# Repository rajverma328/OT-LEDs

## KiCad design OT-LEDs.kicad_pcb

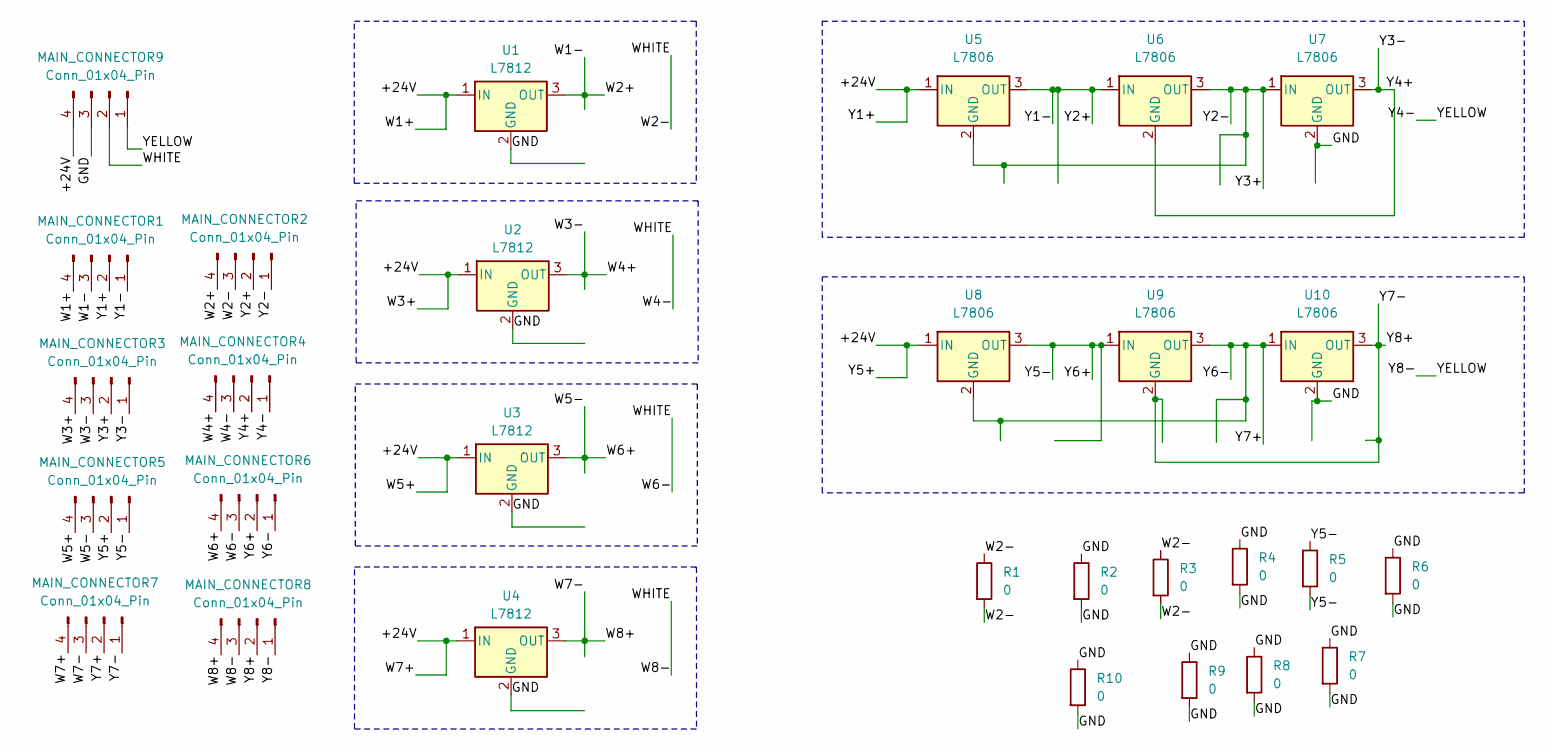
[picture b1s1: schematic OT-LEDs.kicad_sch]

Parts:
MAIN_CONNECTOR1, MAIN_CONNECTOR2, MAIN_CONNECTOR3, MAIN_CONNECTOR4, MAIN_CONNECTOR5, MAIN_CONNECTOR6, MAIN_CONNECTOR7, MAIN_CONNECTOR8, MAIN_CONNECTOR9: Conn_01x04_Pin; FanPinHeader_1x04_P2.54mm_Vertical
R1, R2, R4, R6, R7, R8, R9: 0; R_Axial_DIN0204_L3.6mm_D1.6mm_P5.08mm_Horizontal
R3, R5, R10: 0; R_Axial_DIN0204_L3.6mm_D1.6mm_P7.62mm_Horizontal
U1, U2, U3, U4: L7812; TO-220-3_Vertical
U5, U6, U7, U8, U9, U10: L7806; TO-220-3_Vertical

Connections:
/+24V: MAIN_CONNECTOR1.2, MAIN_CONNECTOR1.4, MAIN_CONNECTOR3.4, MAIN_CONNECTOR5.2, MAIN_CONNECTOR5.4, MAIN_CONNECTOR7.4, MAIN_CONNECTOR9.4, U1.1 (IN), U2.1 (IN), U3.1 (IN), U4.1 (IN), U5.1 (IN), U8.1 (IN)
/GND: MAIN_CONNECTOR9.3, R2.1, R2.2, R4.1, R4.2, R6.1, R6.2, R7.1, R7.2, R8.1, R8.2, R9.1, R9.2, R10.1, R10.2, U1.2 (GND), U2.2 (GND), U3.2 (GND), U4.2 (GND), U7.2 (GND), U10.2 (GND)
/W1-: MAIN_CONNECTOR1.3, MAIN_CONNECTOR2.4, U1.3 (OUT)
/W2-: MAIN_CONNECTOR2.3, MAIN_CONNECTOR4.3, MAIN_CONNECTOR6.3, MAIN_CONNECTOR8.3, MAIN_CONNECTOR9.2, R1.1, R1.2, R3.1, R3.2
/W3-: MAIN_CONNECTOR3.3, MAIN_CONNECTOR4.4, U2.3 (OUT)
/W5-: MAIN_CONNECTOR5.3, MAIN_CONNECTOR6.4, U3.3 (OUT)
/W7-: MAIN_CONNECTOR7.3, MAIN_CONNECTOR8.4, U4.3 (OUT)
/Y1-: MAIN_CONNECTOR1.1, MAIN_CONNECTOR2.2, U5.3 (OUT), U6.1 (IN)
/Y2-: MAIN_CONNECTOR2.1, MAIN_CONNECTOR3.2, U5.2 (GND), U6.3 (OUT), U7.1 (IN)
/Y3-: MAIN_CONNECTOR3.1, MAIN_CONNECTOR4.2, U6.2 (GND), U7.3 (OUT)
/Y4-: MAIN_CONNECTOR4.1, MAIN_CONNECTOR8.1, MAIN_CONNECTOR9.1
/Y5-: MAIN_CONNECTOR5.1, MAIN_CONNECTOR6.2, R5.1, R5.2, U8.3 (OUT), U9.1 (IN)
/Y6-: MAIN_CONNECTOR6.1, MAIN_CONNECTOR7.2, U8.2 (GND), U9.3 (OUT), U10.1 (IN)
/Y7-: MAIN_CONNECTOR7.1, MAIN_CONNECTOR8.2, U9.2 (GND), U10.3 (OUT)

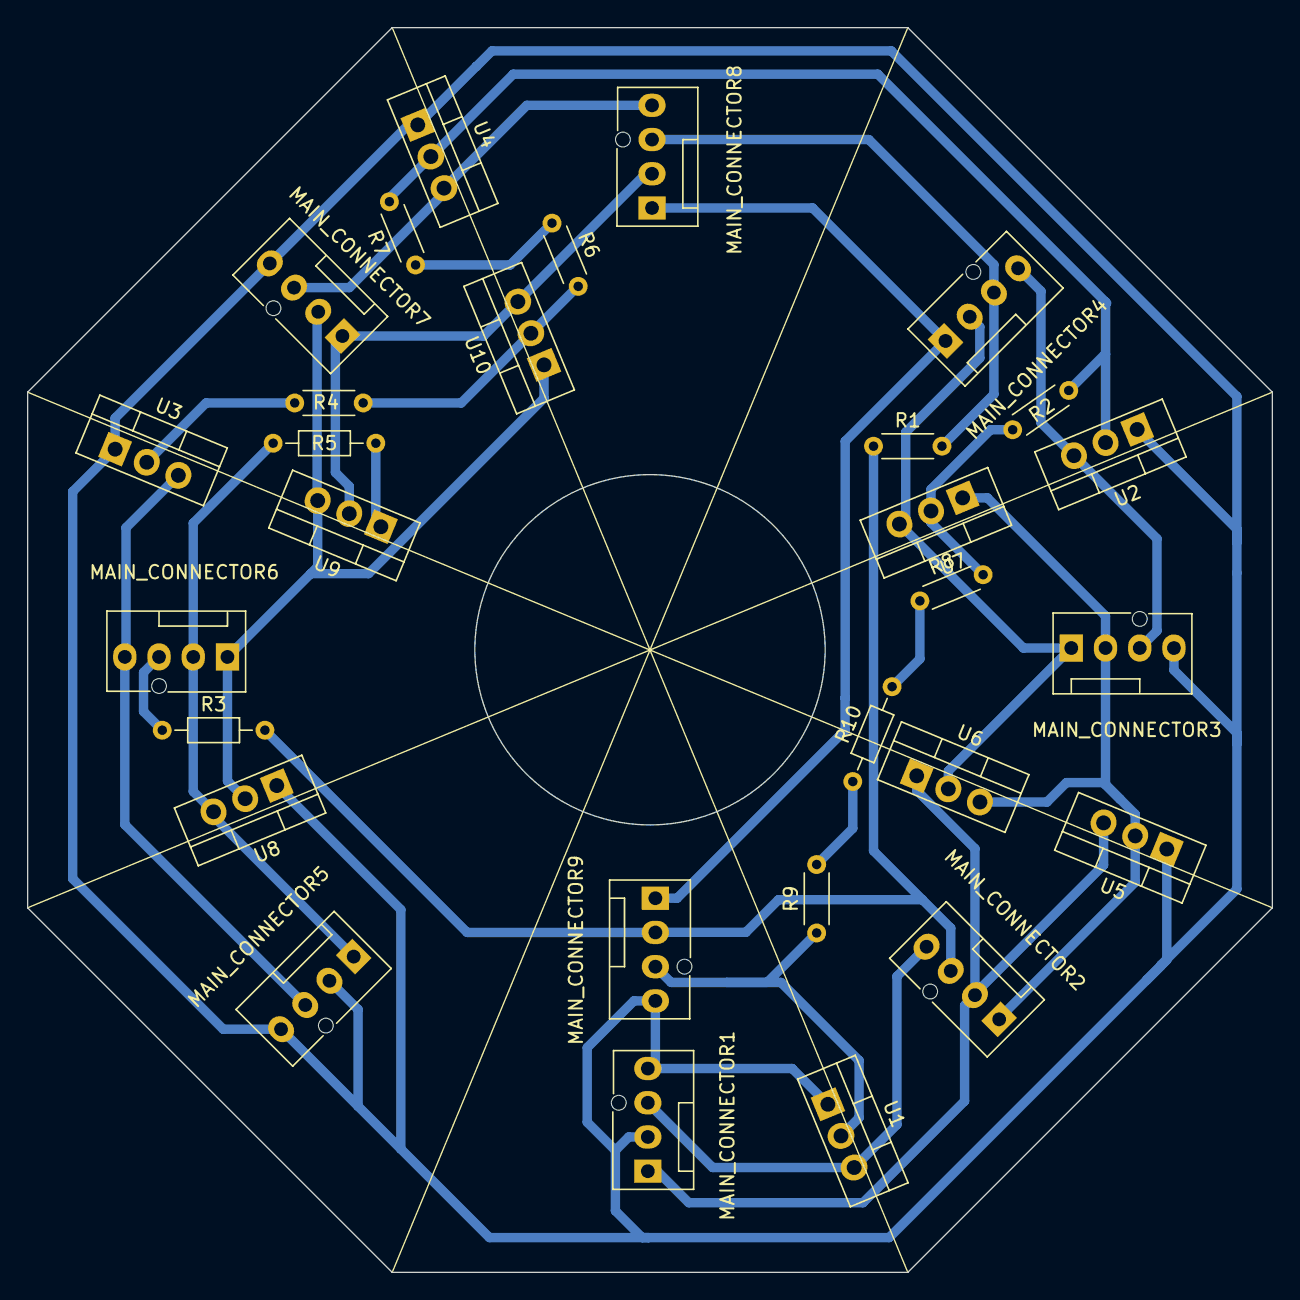
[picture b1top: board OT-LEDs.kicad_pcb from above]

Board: 2 copper layers, 92.4 x 92.4 mm, 29 parts (0 on the bottom side), 14 nets.
